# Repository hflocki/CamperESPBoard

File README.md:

# CamperESP Board

⚠️ **STATUS: WORK IN PROGRESS (In Arbeit)** ⚠️  
*Dieses Projekt befindet sich aktuell noch in der Entwicklung und Testphase. Schaltpläne und Layouts können sich jederzeit ändern. Die Verwendung der Daten erfolgt auf eigene Gefahr.*

---

Das Board basiert auf einem **ESP32** und dient zur flexiblen Erfassung von Sensordaten (z. B. Temperatur, Füllstände) und zur Steuerung von Verbrauchern im Fahrzeug über eine integrierte Transistorschaltstufe.

Das Layout wurde maximal geschrumpft, um perfekt in das ultrakompakte **Spelsberg Mini 25-L/w Gehäuse** (Maße: 89 x 43 x 38 mm) zu passen.

---

## Features

- **Spannungsversorgung:** Robuster Step-Down-Regler (TPS5430) für die raue 12V-Camper-Bordnetzumgebung (mit Sicherung `F1` und Verpolungsschutz `D2`).
- **Kompakte Ausgänge:** 2,54 mm Lochreihen (Pin Header) statt klobiger Klemmen für maximale Platzersparnis und Rüttelfestigkeit.
- **Relais-/Schaltstufe:** Integrierter Transistor (`Q1`) an `GPIO10` zum direkten Schalten kleinerer Verbraucher oder Relais.
- **Schnittstellen:** Voller Hardware-I2C-Bus sowie UART (RX/TX) für die Kommunikation mit Displays, Sensoren oder Victron-Geräten.

---

## Pinbelegung (Pinout)

Die Anschlüsse sind logisch auf zwei einreihige Lochleisten (2,54 mm Raster) am rechten Rand aufgeteilt:

### Leiste 1 (J5) – Stromversorgung & I2C Bus
| Pin | Bezeichnung | Beschreibung |
|:---:|:------------|:-------------|
| 1   | **12V** | Abgesicherter 12V-Ausgang für externe Geräte |
| 2   | **5V** | 5V Versorgungsspannung (VDD) |
| 3   | **3V3** | Saubere 3,3V Logikspannung |
| 4   | **GND** | Gemeinsame Fahrzeugmasse (Minuspol) |
| 5   | **SDA** | I2C Datenleitung (`GPIO4`) |
| 6   | **SCL** | I2C Taktleitung (`GPIO5`) |
| 7   | **G0** | Universal Digital I/O (`GPIO0`) / z.B. OneWire |
| 8   | **G1** | Universal Digital I/O (`GPIO1`) |

### Leiste 2 (J6) – GPIOs & UART
| Pin | Bezeichnung | Beschreibung |
|:---:|:------------|:-------------|
| 1   | **G2** | Universal Digital I/O (`GPIO2`) |
| 2   | **G3** | Universal Digital I/O (`GPIO3`) |
| 3   | **REL** | Relais-Steuerpin (`GPIO10` über Transistorstufe) |
| 4   | **RX** | Serieller Empfangskanal (`GPIO20`) |
| 5   | **TX** | Serieller Sendekanal (`GPIO21`) |
| 6   | *NC* | Frei / Reserve |
| 7   | *NC* | Frei / Reserve |
| 8   | *NC* | Frei / Reserve |

---

## Projektstruktur für GitHub

Dieses Repository enthält alle benötigten KiCad-Quelldateien:

- `CamperESP.kicad_pro` - KiCad Projekt-Hauptdatei
- `CamperESP.kicad_sch` - Schaltplan (Schematic) mit optimiertem Label-Wiring
- `CamperESP.kicad_pcb` - Platinen-Layout (PCB) optimiert für Spelsberg-Gehäuse
- `fp-lib-table` & `sym-lib-table` - Lokale Bibliotheksverweise für benutzte Custom-Bauteile

---

## Einbau- & Löthinweise

1. **Leiterbahnen:** Die Leitungen für `12V`, `5V` und `GND` im Layout mit mindestens **1.0 mm bis 1.5 mm** Breite ausführen, um ausreichende Stromtragfähigkeit im Camper zu gewährleisten.
2. **Kabelanschluss:** Kabel können entweder direkt in die Platinenlöcher eingelötet werden (maximale Rüttelfestigkeit im Fahrbetrieb) oder über eine klassische 2,54 mm Stiftleiste steckbar gemacht werden.

---

## Haftungsausschluss (Disclaimer)

**Haftungsausschluss für Bastler- und DIY-Projekte:**

Die hier bereitgestellten Inhalte, Schaltpläne und Layouts dienen ausschließlich zu Informations- und privaten Bildungszwecken. 

1. **Keine Haftung:** Ich übernehme keinerlei Haftung für Schäden jeglicher Art (einschließlich, aber nicht beschränkt auf Sachschäden, Personenschäden, Fahrzeugbrände oder finanzielle Verluste), die direkt oder indirekt durch den Nachbau, die Nutzung oder Fehlfunktionen dieser Schaltung entstehen.
2. **Eigene Verantwortung:** Das Arbeiten an der Fahrzeugelektrik und Elektronik erfolgt vollständig auf eigene Gefahr und Verantwortung des Ausführenden. 
3. **KFZ-Vorschriften:** Es liegt in der Verantwortung des Nachbauers, für eine fachgerechte Absicherung (Sicherungen, Kabelquerschnitte) zu sorgen und alle geltenden Sicherheitsvorschriften sowie KFZ-Richtlinien einzuhalten.

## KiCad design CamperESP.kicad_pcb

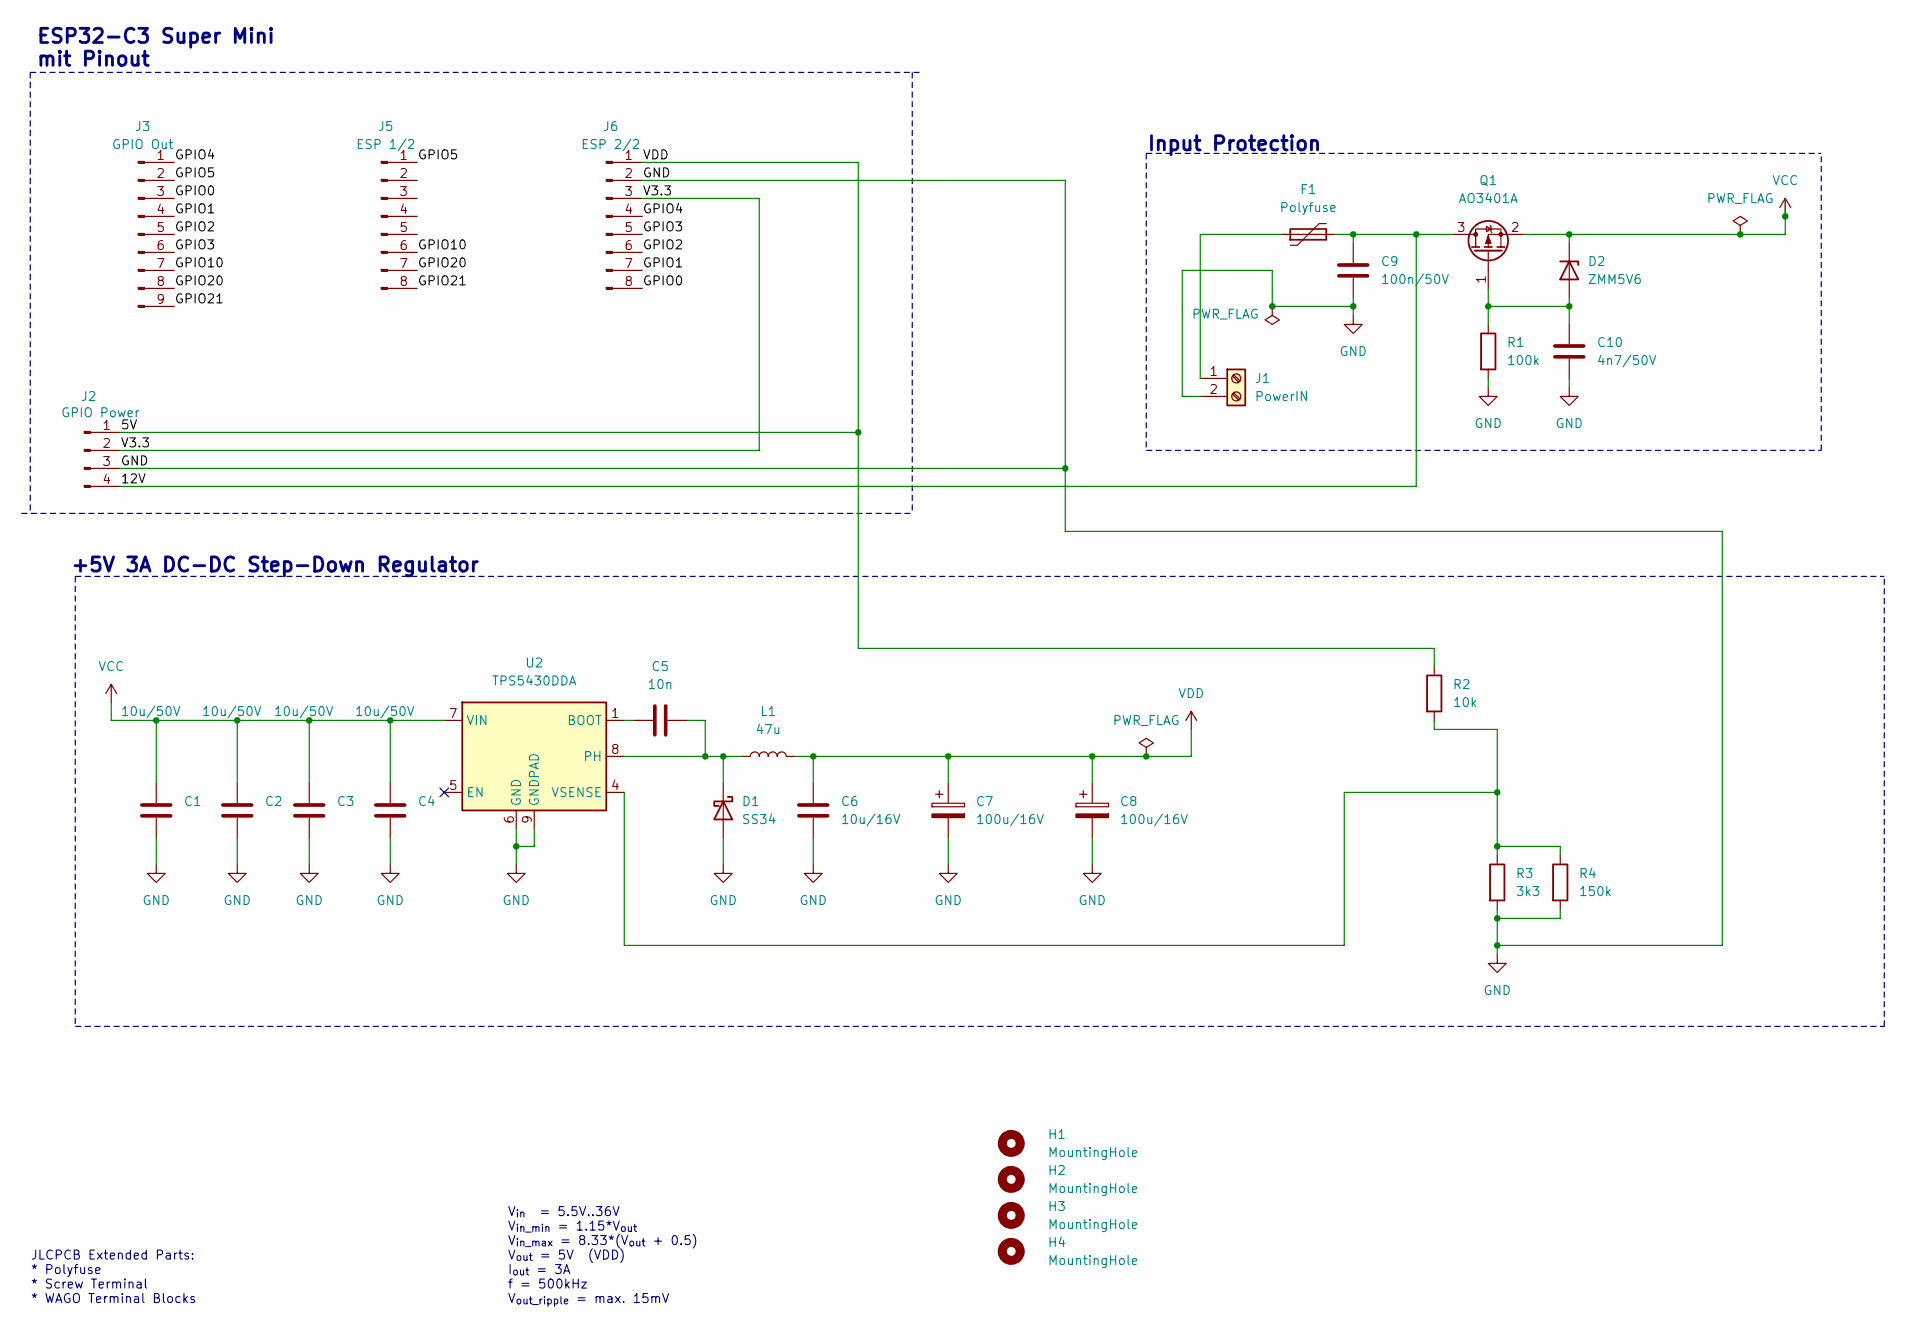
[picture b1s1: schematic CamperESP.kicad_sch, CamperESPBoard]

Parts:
C1, C2, C3, C4: 10u/50V; C_1206_3216Metric; MPN CL31A106KBHNNNE; LCSC C13585
C5: 10n; C_0402_1005Metric; MPN CL05B103KB5NNNC; LCSC C15195
C6: 10u/16V; C_0402_1005Metric; MPN CL05A106MQ5NUNC; LCSC C15525
C7, C8: 100u/16V; CP_EIA-3528-21_Kemet-B; MPN TAJB107K006RNJ; LCSC C16133
C9: 100n/50V; C_0603_1608Metric; MPN CC0603KRX7R9BB104; LCSC C14663
C10: 4n7/50V; C_0402_1005Metric; MPN 0402B472K500NT; LCSC C1538
D1: SS34; D_SMA; MPN SS34; LCSC C8678
D2: ZMM5V6; D_MiniMELF; MPN ZMM5V6; LCSC C8062
F1: Polyfuse; Fuse_1206_3216Metric; MPN 1206L300SLTHYR; LCSC C207041
H1, H2, H3, H4: MountingHole; MountingHole_2.2mm_M2_ISO7380
J1: PowerIN; TerminalBlock_WAGO_236-102_1x02_P5.00mm_45Degree
J2: GPIO Power; PinHeader_1x04_P2.54mm_Vertical
J3: GPIO Out; PinHeader_1x09_P2.54mm_Vertical
J5: ESP 1/2; PinHeader_1x08_P2.54mm_Vertical
J6: ESP 2/2; PinHeader_1x08_P2.54mm_Vertical
L1: 47u; L_12x12mm_H8mm; MPN MWSA1004S-470MT; LCSC C408491
Q1: AO3401A; SOT-23; MPN AO3401A; LCSC C15127
R1: 100k; R_0402_1005Metric; MPN 0402WGF1003TCE; LCSC C25741
R2: 10k; R_0402_1005Metric; MPN 0402WGF1002TCE; LCSC C25744
R3: 3k3; R_0402_1005Metric; MPN 0402WGF3301TCE; LCSC C25890
R4: 150k; R_0402_1005Metric; MPN 0402WGF1503TCE; LCSC C25755
U2: TPS5430DDA; TI_SO-PowerPAD-8_ThermalVias; MPN TPS5430DDAR; JLC LSOP-8_EP_3.9x4.9x1.27P

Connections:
/12V: C9.1, F1.2, J2.4, Q1.3 (D)
/GPIO0: J3.3, J6.8
/GPIO1: J3.4, J6.7
/GPIO2: J3.5, J6.6
/GPIO3: J3.6, J6.5
/GPIO4: J3.1, J6.4
/GPIO5: J3.2, J5.1
/GPIO10: J3.7, J5.6
/GPIO20: J3.8, J5.7
/GPIO21: J3.9, J5.8
/V3.3: J2.2, J6.3
GND: C1.2, C2.2, C3.2, C4.2, C6.2, C7.2, C8.2, C9.2, C10.2, D1.2 (A), J1.2, J2.3, J6.2, R1.2, R3.2, R4.2, U2.6 (GND), U2.9 (GNDPAD)
unnamed: C5.2, D1.1 (K), L1.1, U2.8 (PH)
unnamed: C10.1, D2.2 (A), Q1.1 (G), R1.1
unnamed: F1.1, J1.1
unnamed: C5.1, U2.1 (BOOT)
unnamed: R2.2, R3.1, R4.1, U2.4 (VSENSE)
VCC: C1.1, C2.1, C3.1, C4.1, D2.1 (K), Q1.2 (S), U2.7 (VIN)
VDD: C6.1, C7.1, C8.1, J2.1, J6.1, L1.2, R2.1

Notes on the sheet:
V_{in} = 5.5V..36V V_{in_min} = 1.15*V_{out} V_{in_max} = 8.33*(V_{out} + 0.5) V_{out} = 5V (VDD) I_{out} = 3A f = 500kHz V_{out_ripple} = max. 15mV
Input Protection
ESP32-C3 Super Mini mit Pinout
JLCPCB Extended Parts: * Polyfuse * Screw Terminal * WAGO Terminal Blocks
+5V 3A DC-DC Step-Down Regulator

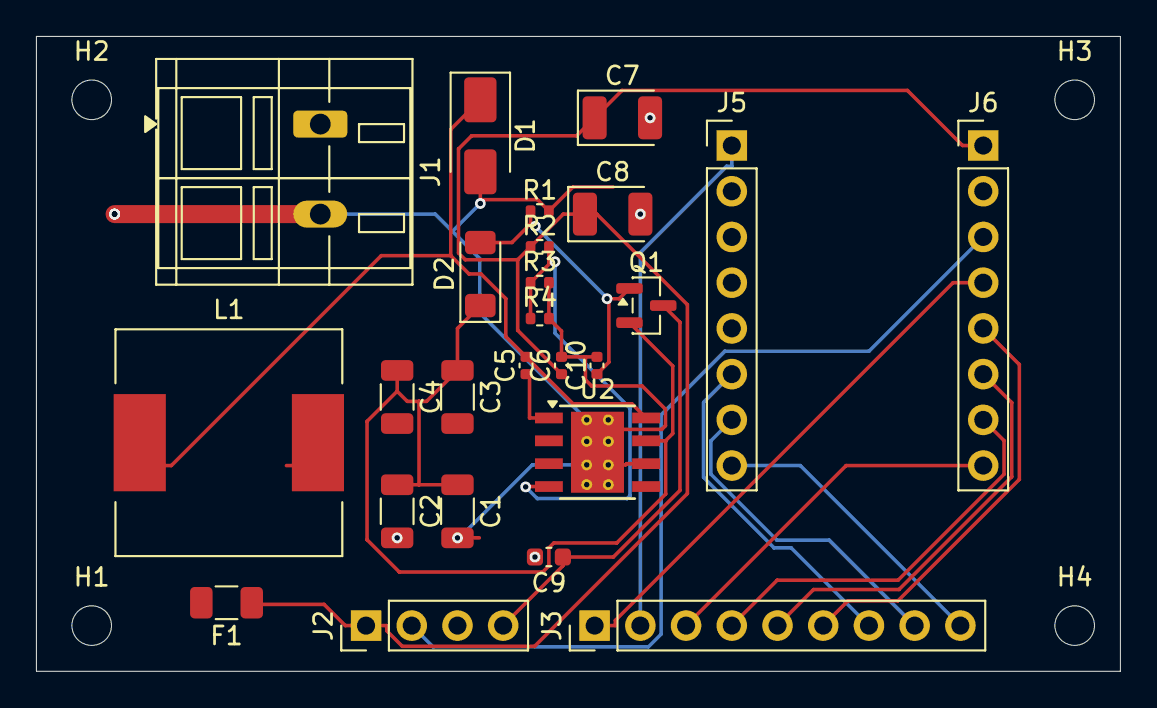
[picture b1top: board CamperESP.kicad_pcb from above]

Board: 2 copper layers, 60.2 x 35.3 mm, 29 parts (0 on the bottom side), 19 nets.
